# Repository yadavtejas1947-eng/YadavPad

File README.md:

# YadavPad
This is a 3 by 3 matrix macropad .

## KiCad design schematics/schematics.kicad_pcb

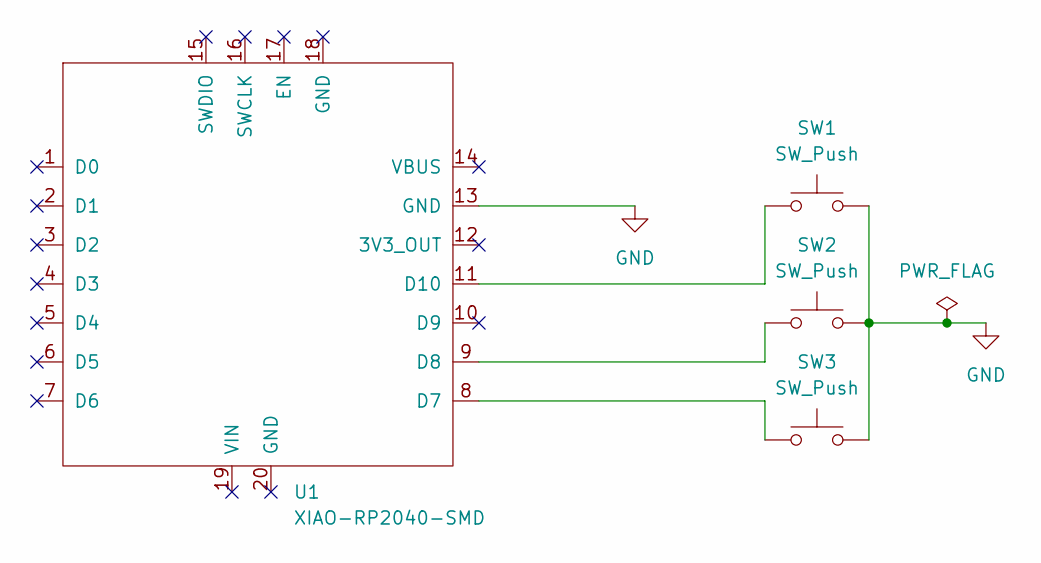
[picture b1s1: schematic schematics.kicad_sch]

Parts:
SW1, SW2, SW3: SW_Push; SW_Cherry_MX_1.00u_PCB
U1: XIAO-RP2040-SMD

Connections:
GND: SW1.2, SW2.2, SW3.2, U1.13 (GND)
unnamed: SW3.1, U1.8 (D7)
unnamed: SW2.1, U1.9 (D8)
unnamed: SW1.1, U1.11 (D10)

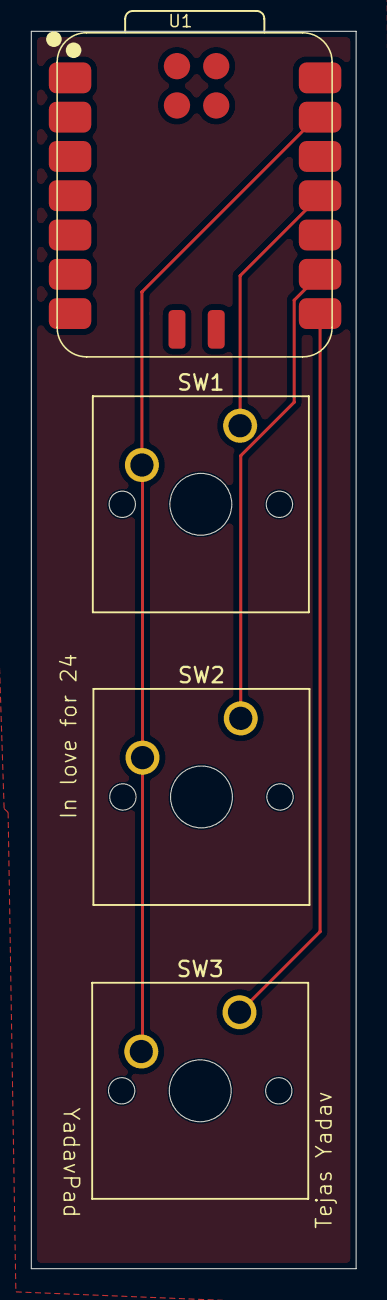
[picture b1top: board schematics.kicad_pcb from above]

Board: 2 copper layers, 21.0 x 80.0 mm, 4 parts (0 on the bottom side), 4 nets.
